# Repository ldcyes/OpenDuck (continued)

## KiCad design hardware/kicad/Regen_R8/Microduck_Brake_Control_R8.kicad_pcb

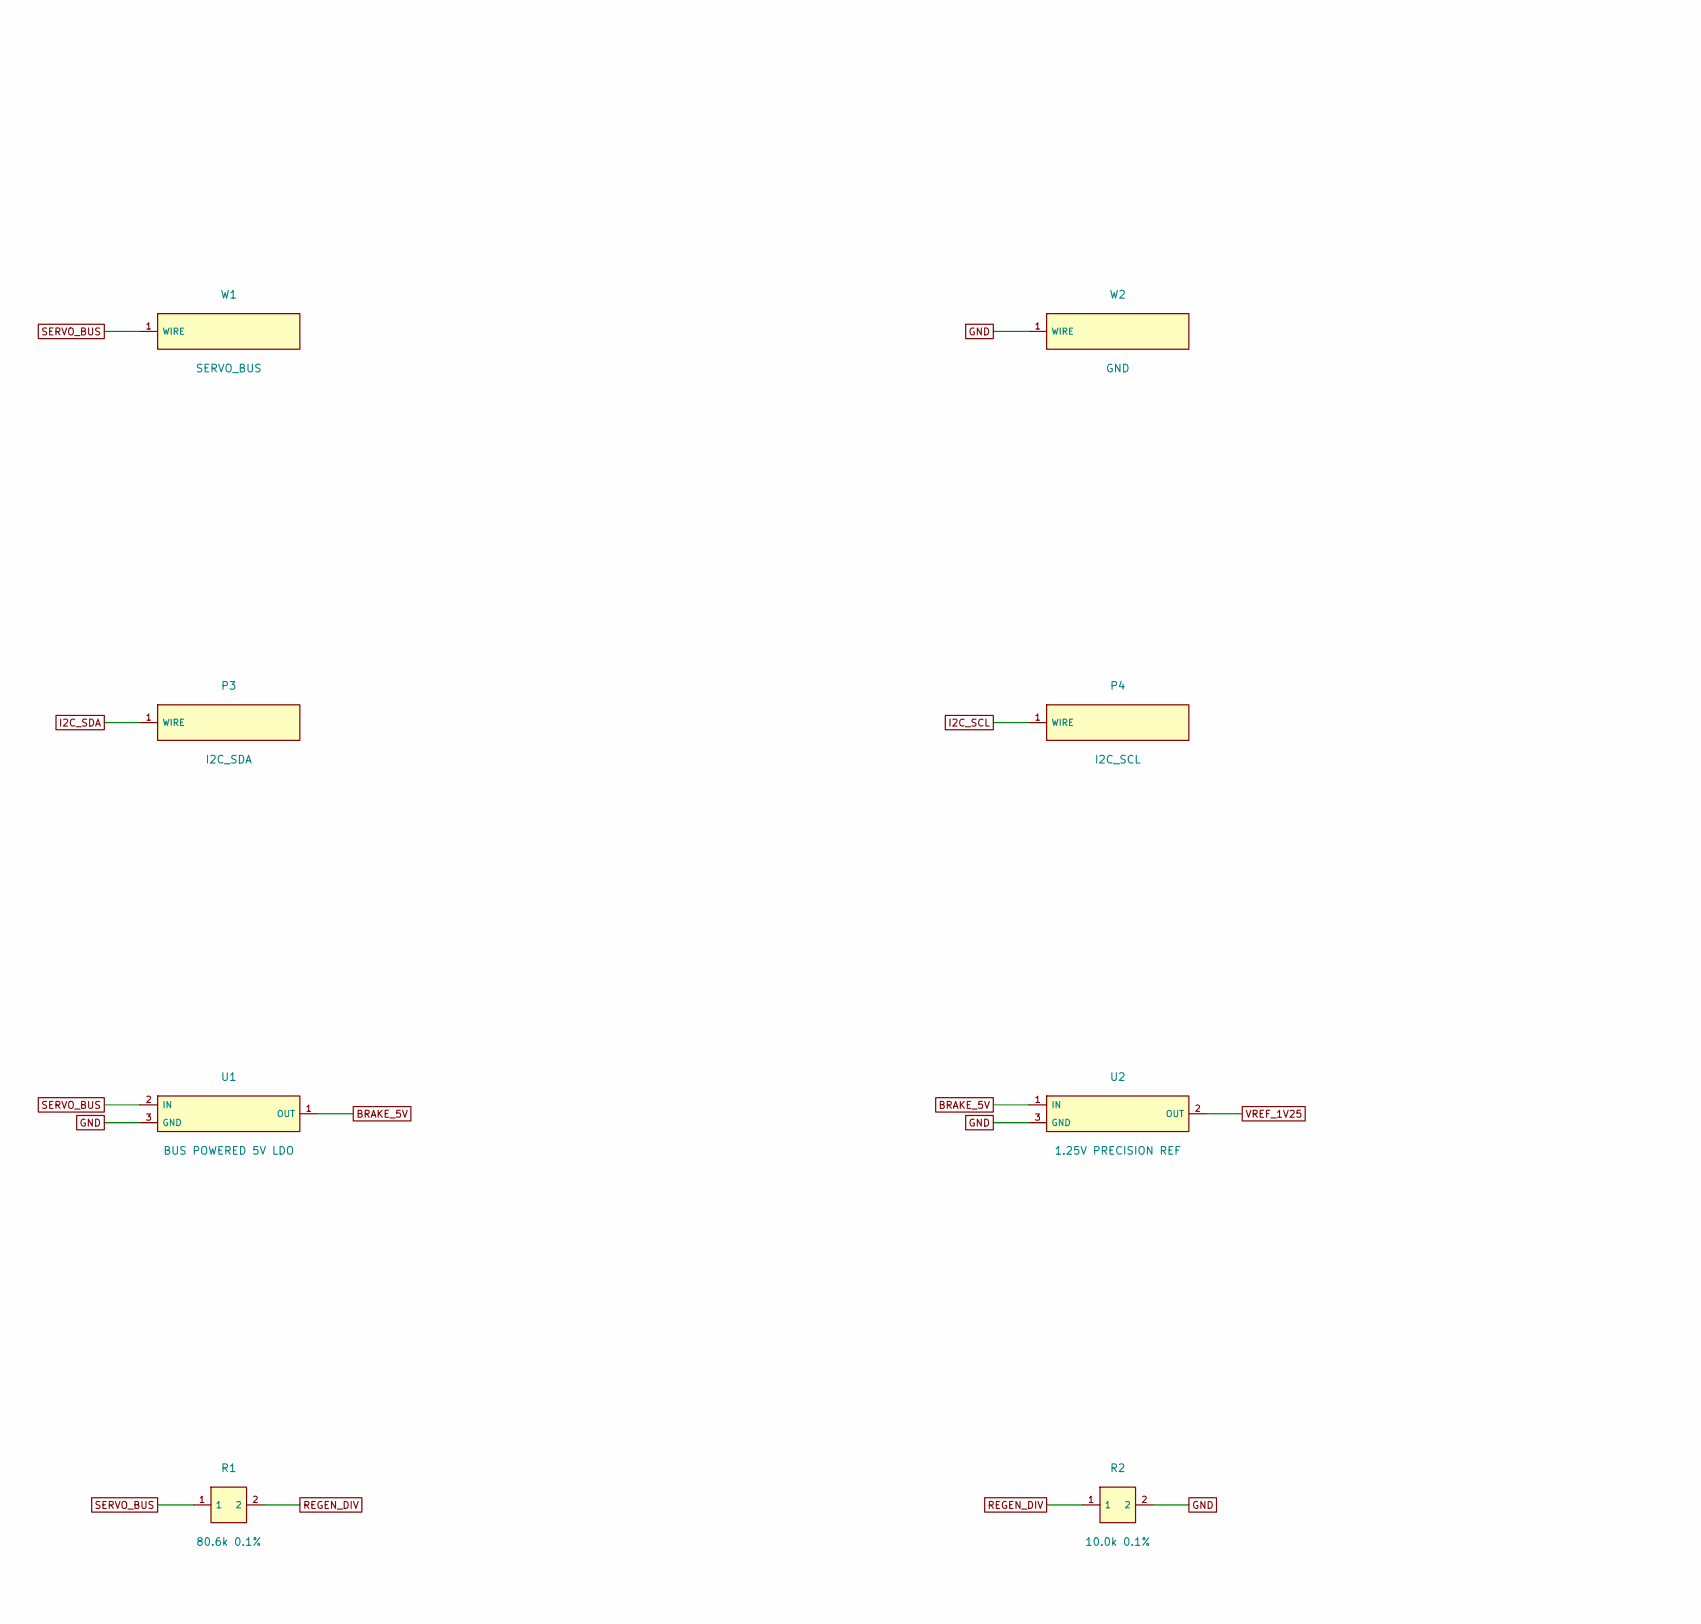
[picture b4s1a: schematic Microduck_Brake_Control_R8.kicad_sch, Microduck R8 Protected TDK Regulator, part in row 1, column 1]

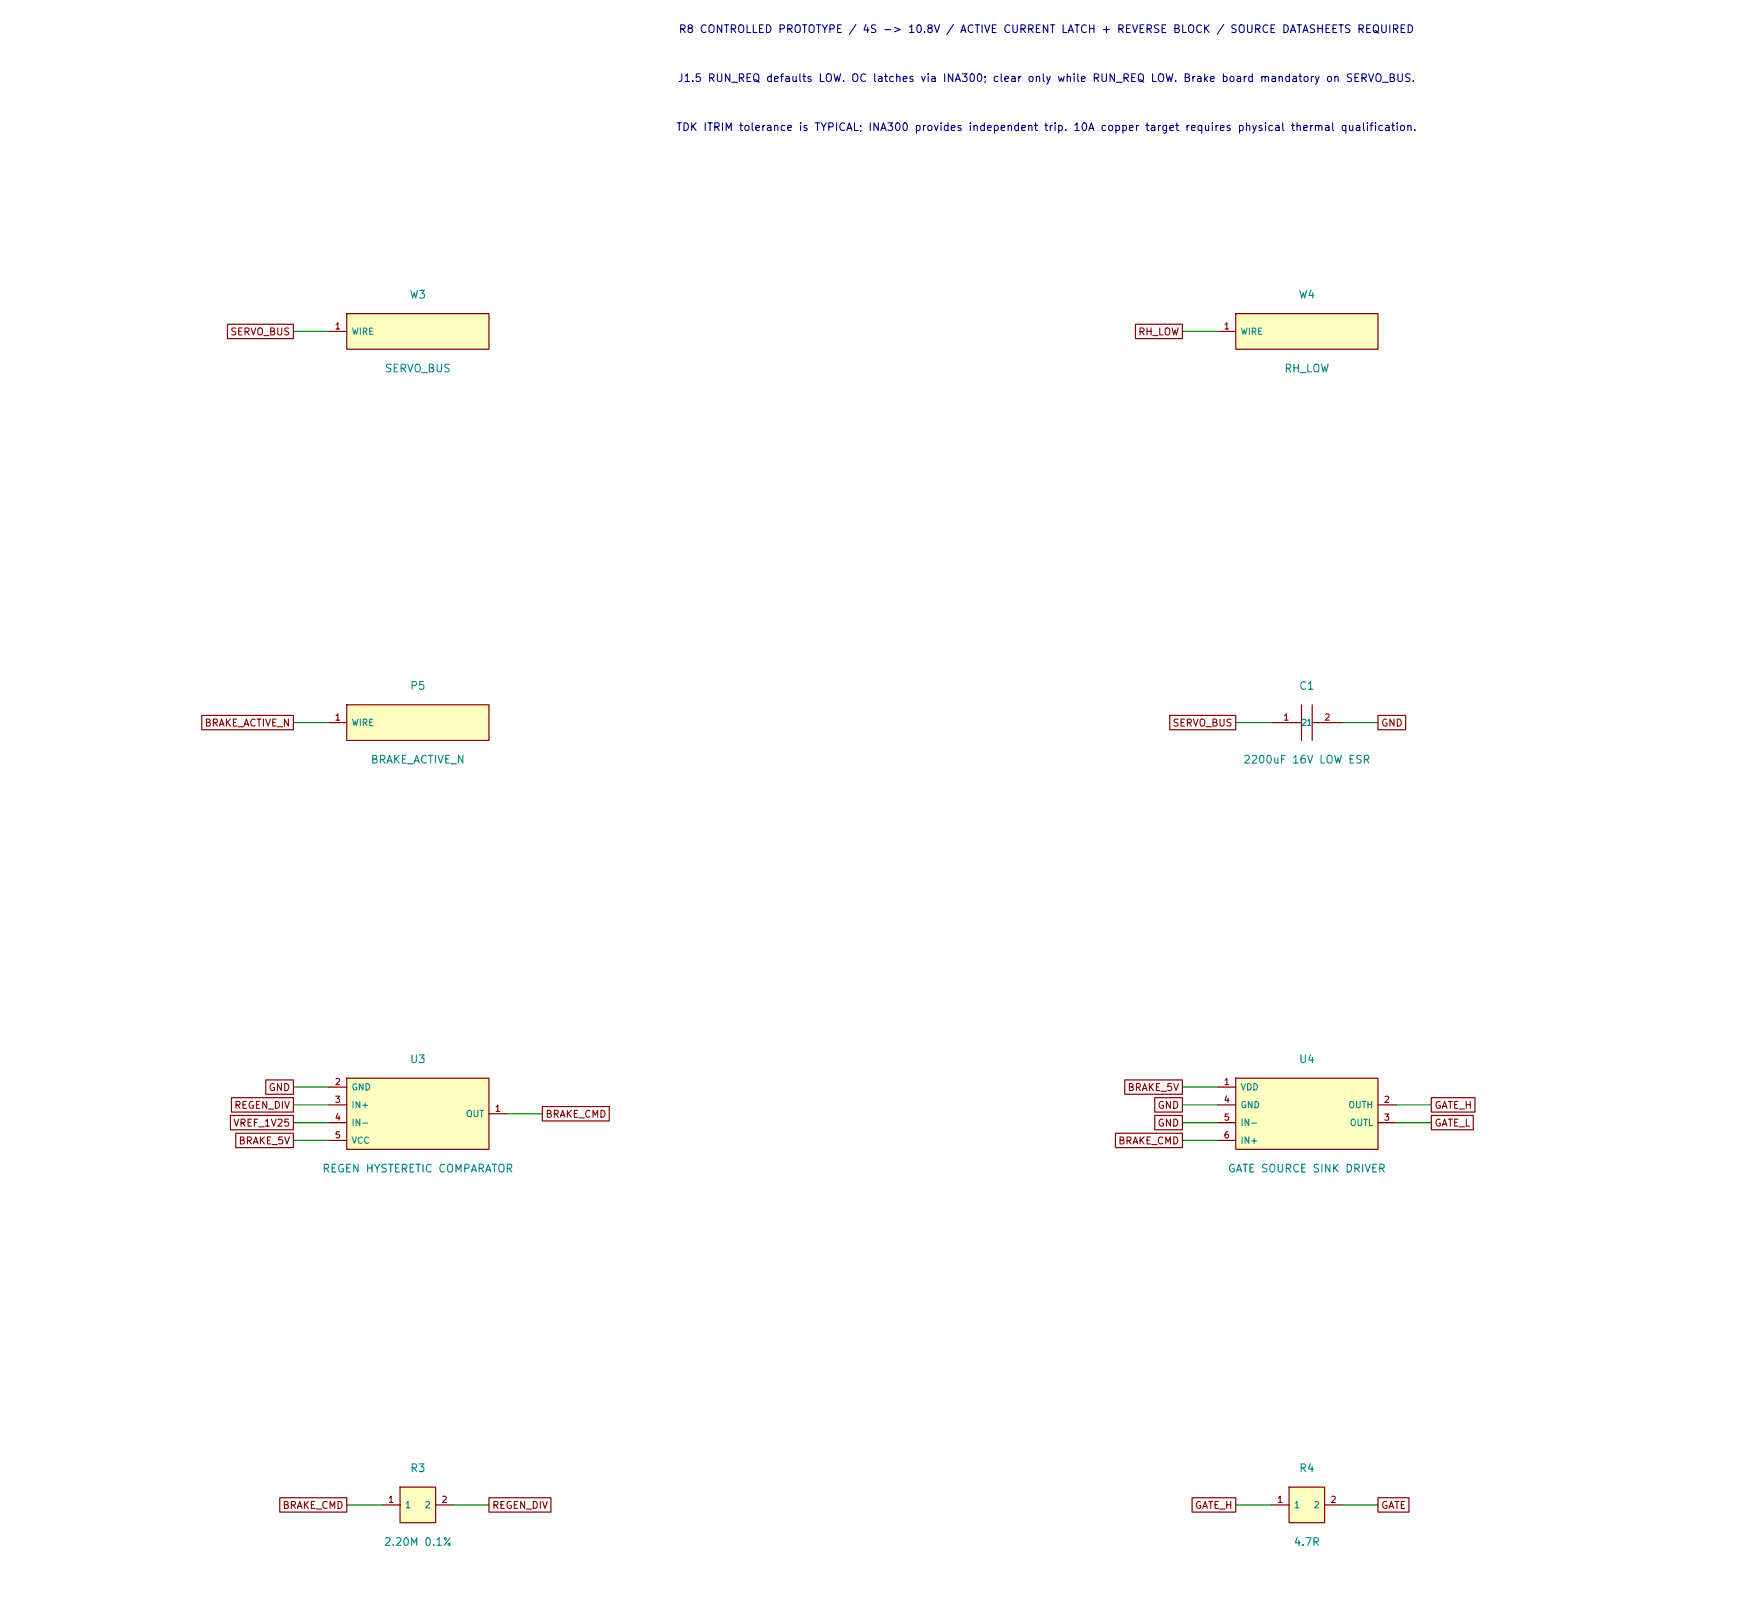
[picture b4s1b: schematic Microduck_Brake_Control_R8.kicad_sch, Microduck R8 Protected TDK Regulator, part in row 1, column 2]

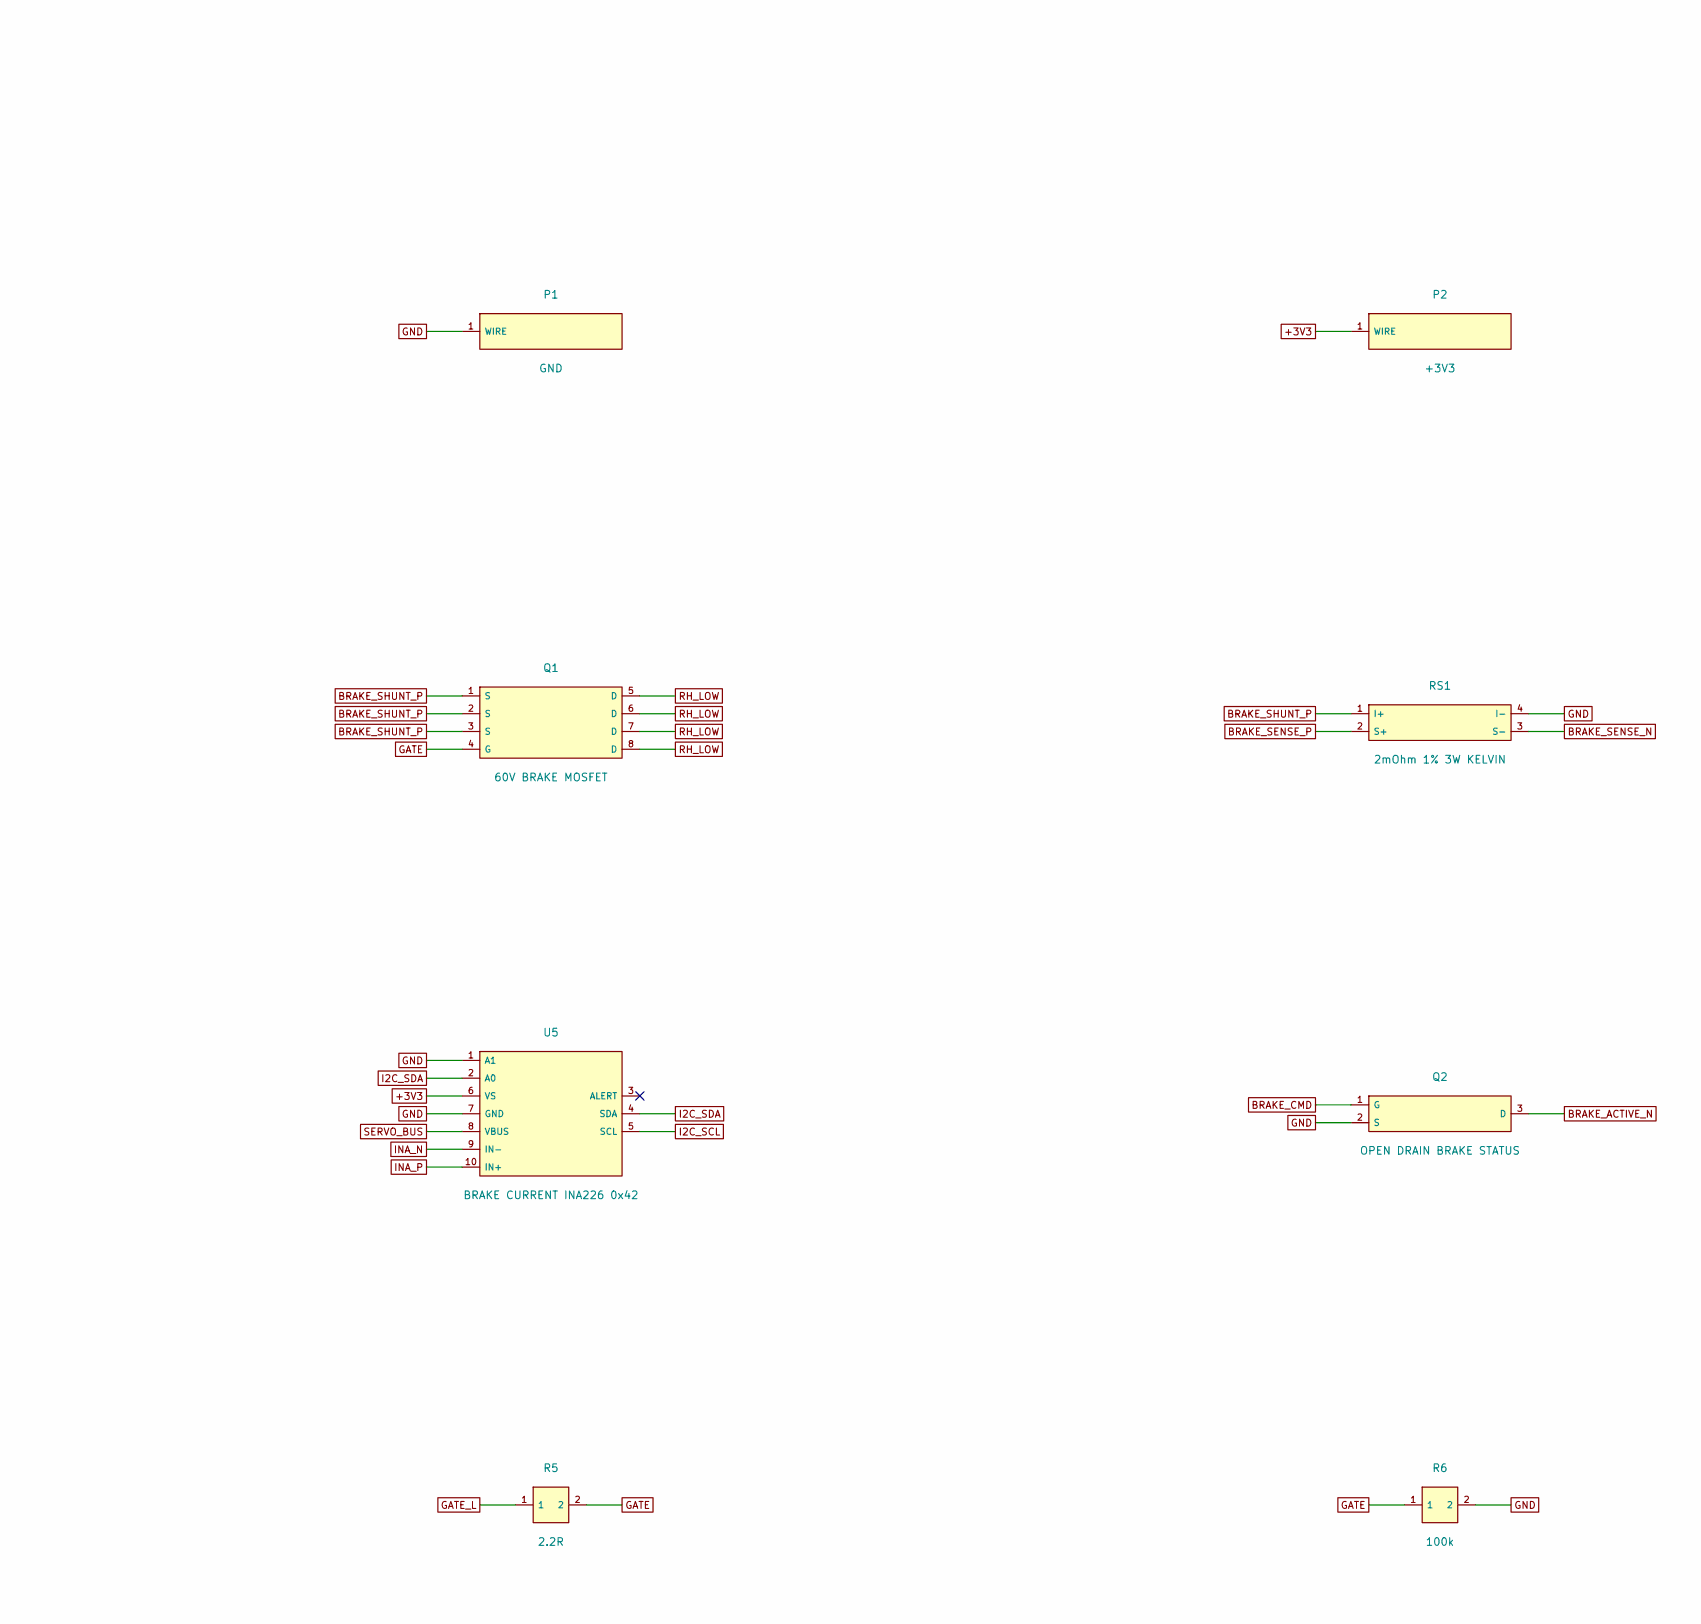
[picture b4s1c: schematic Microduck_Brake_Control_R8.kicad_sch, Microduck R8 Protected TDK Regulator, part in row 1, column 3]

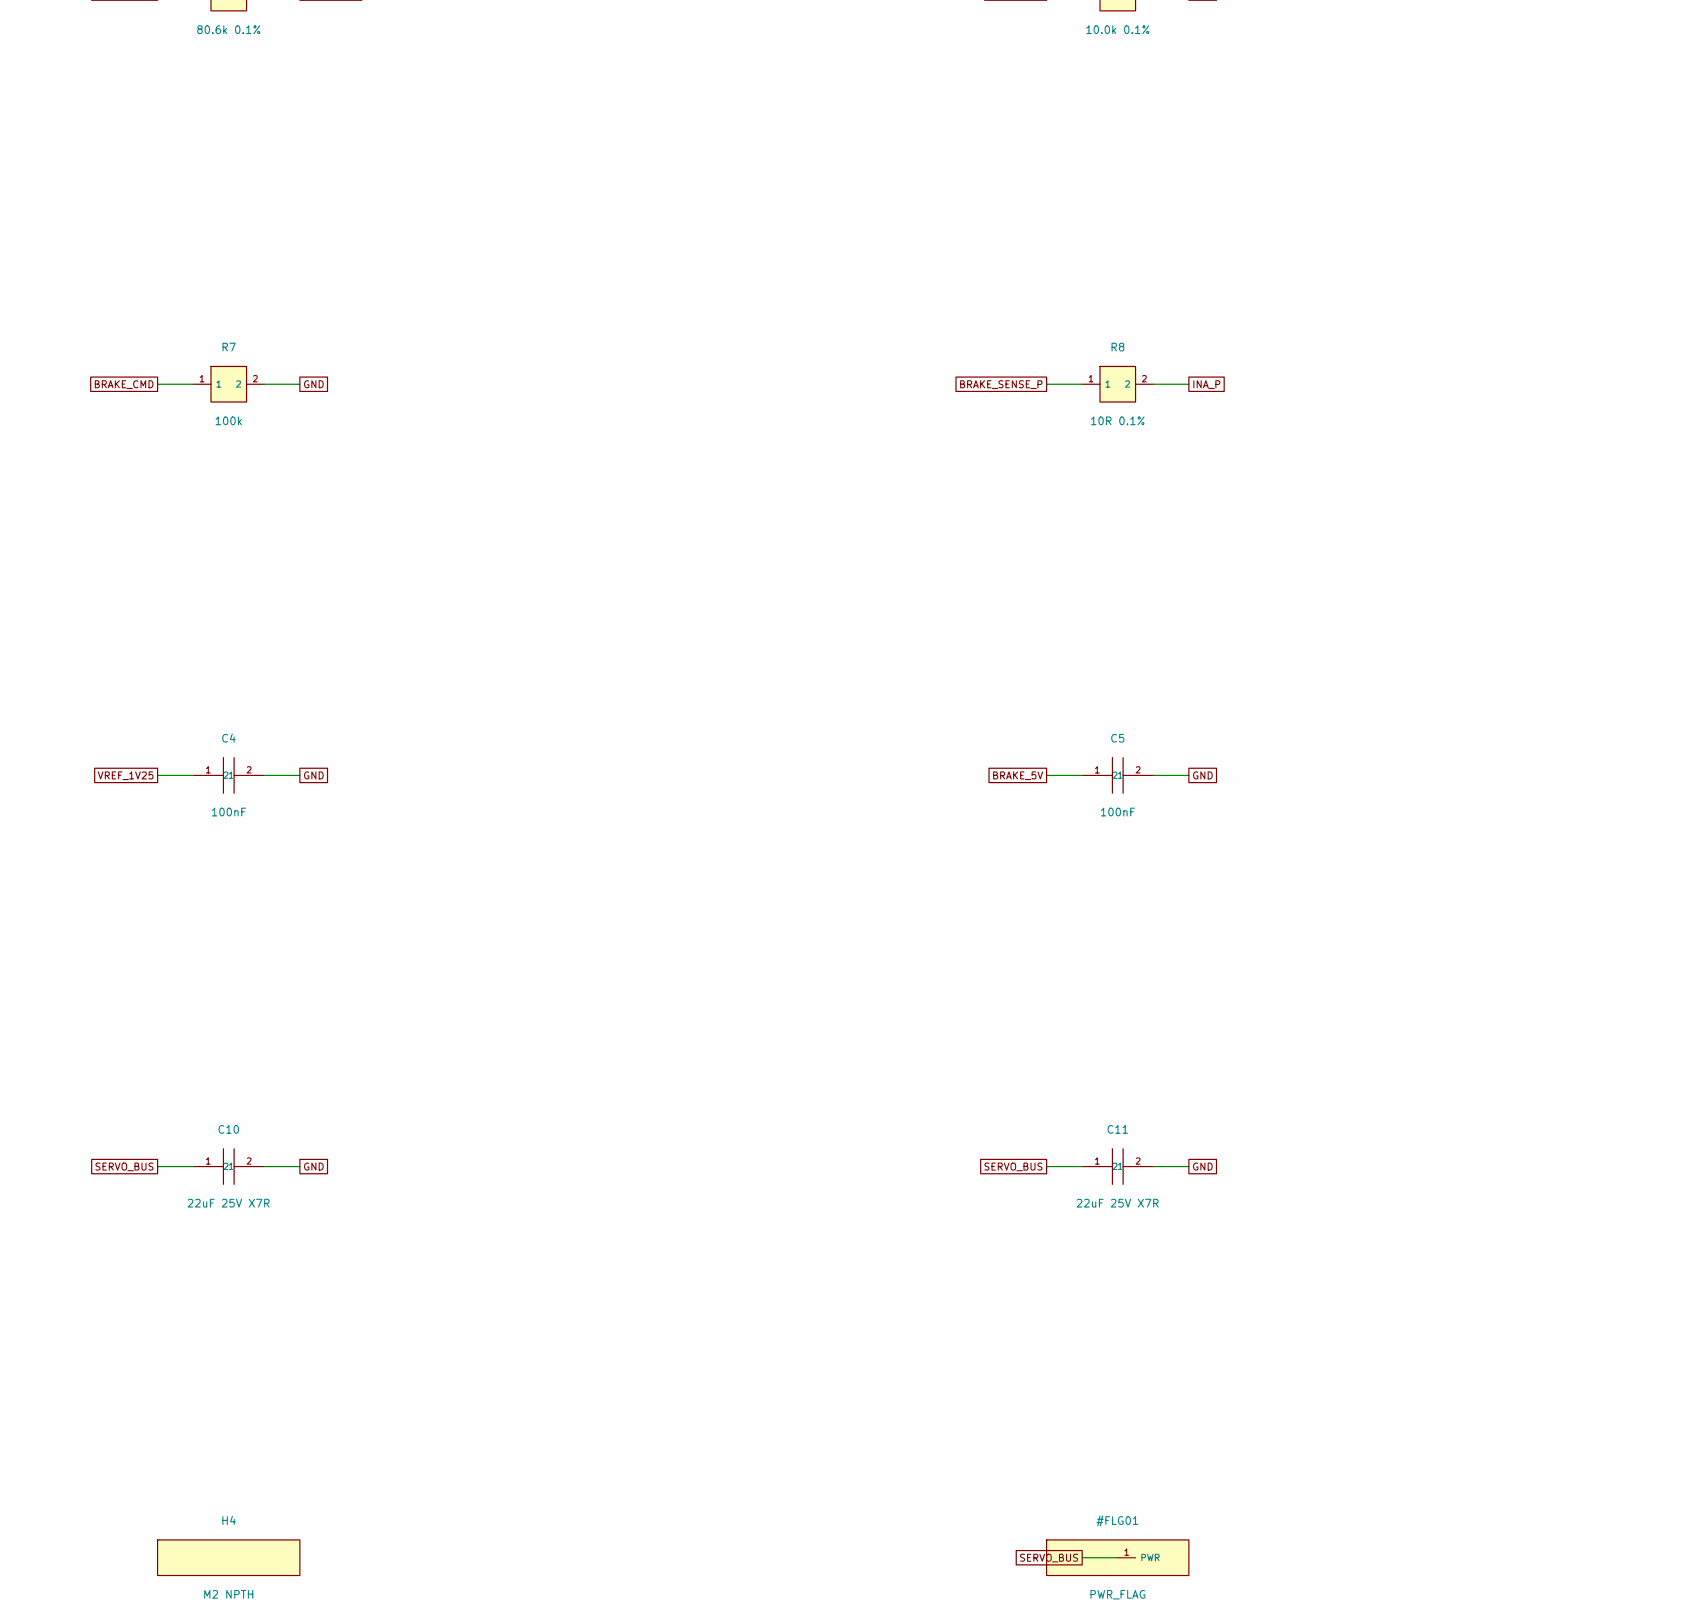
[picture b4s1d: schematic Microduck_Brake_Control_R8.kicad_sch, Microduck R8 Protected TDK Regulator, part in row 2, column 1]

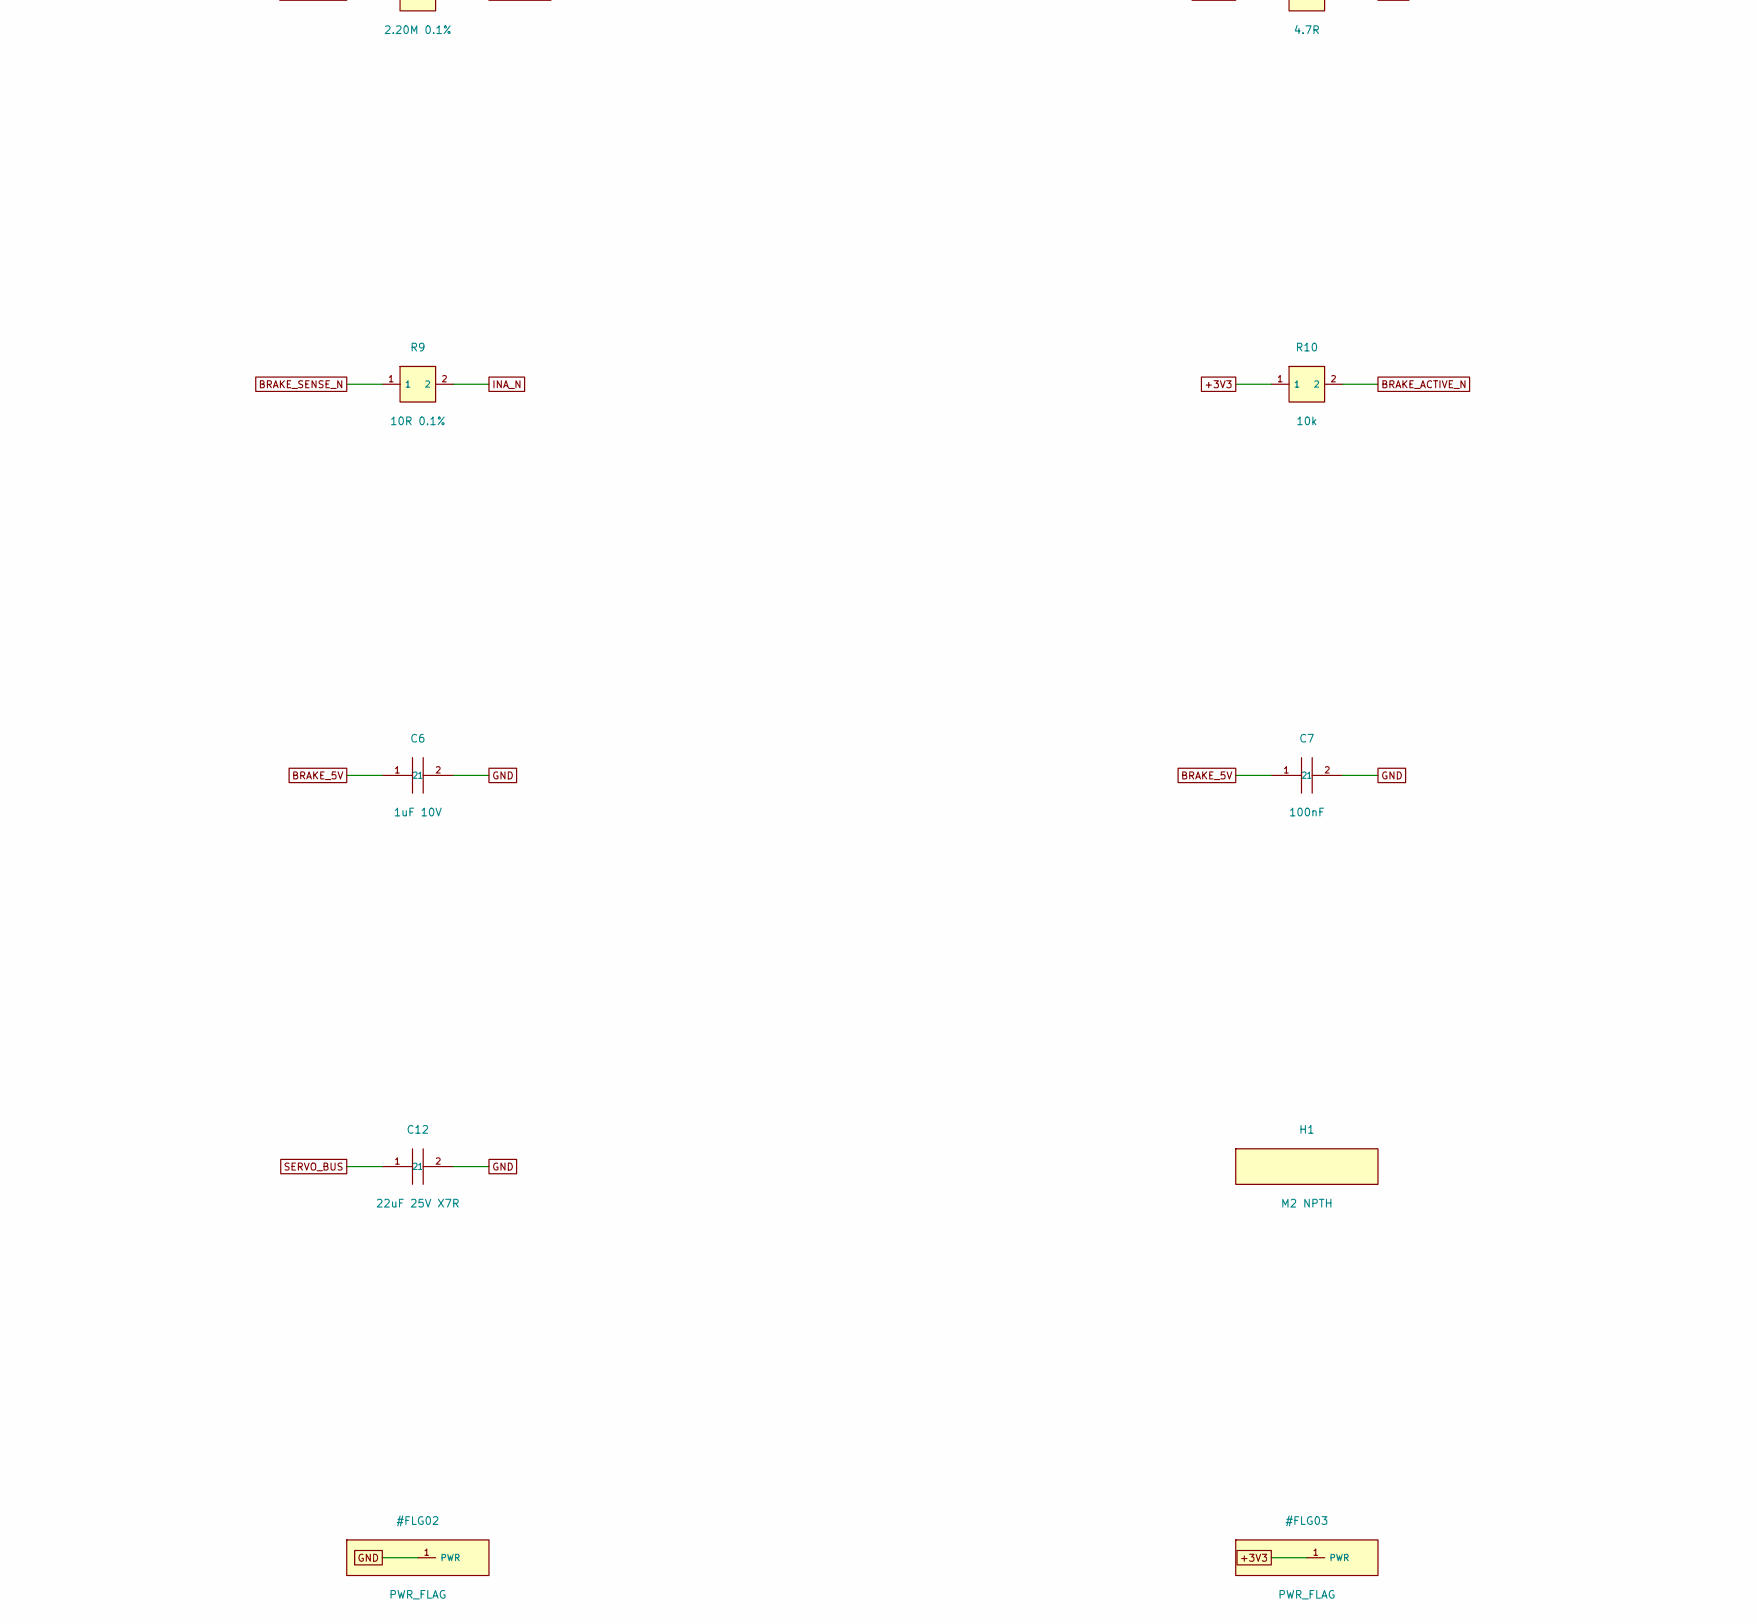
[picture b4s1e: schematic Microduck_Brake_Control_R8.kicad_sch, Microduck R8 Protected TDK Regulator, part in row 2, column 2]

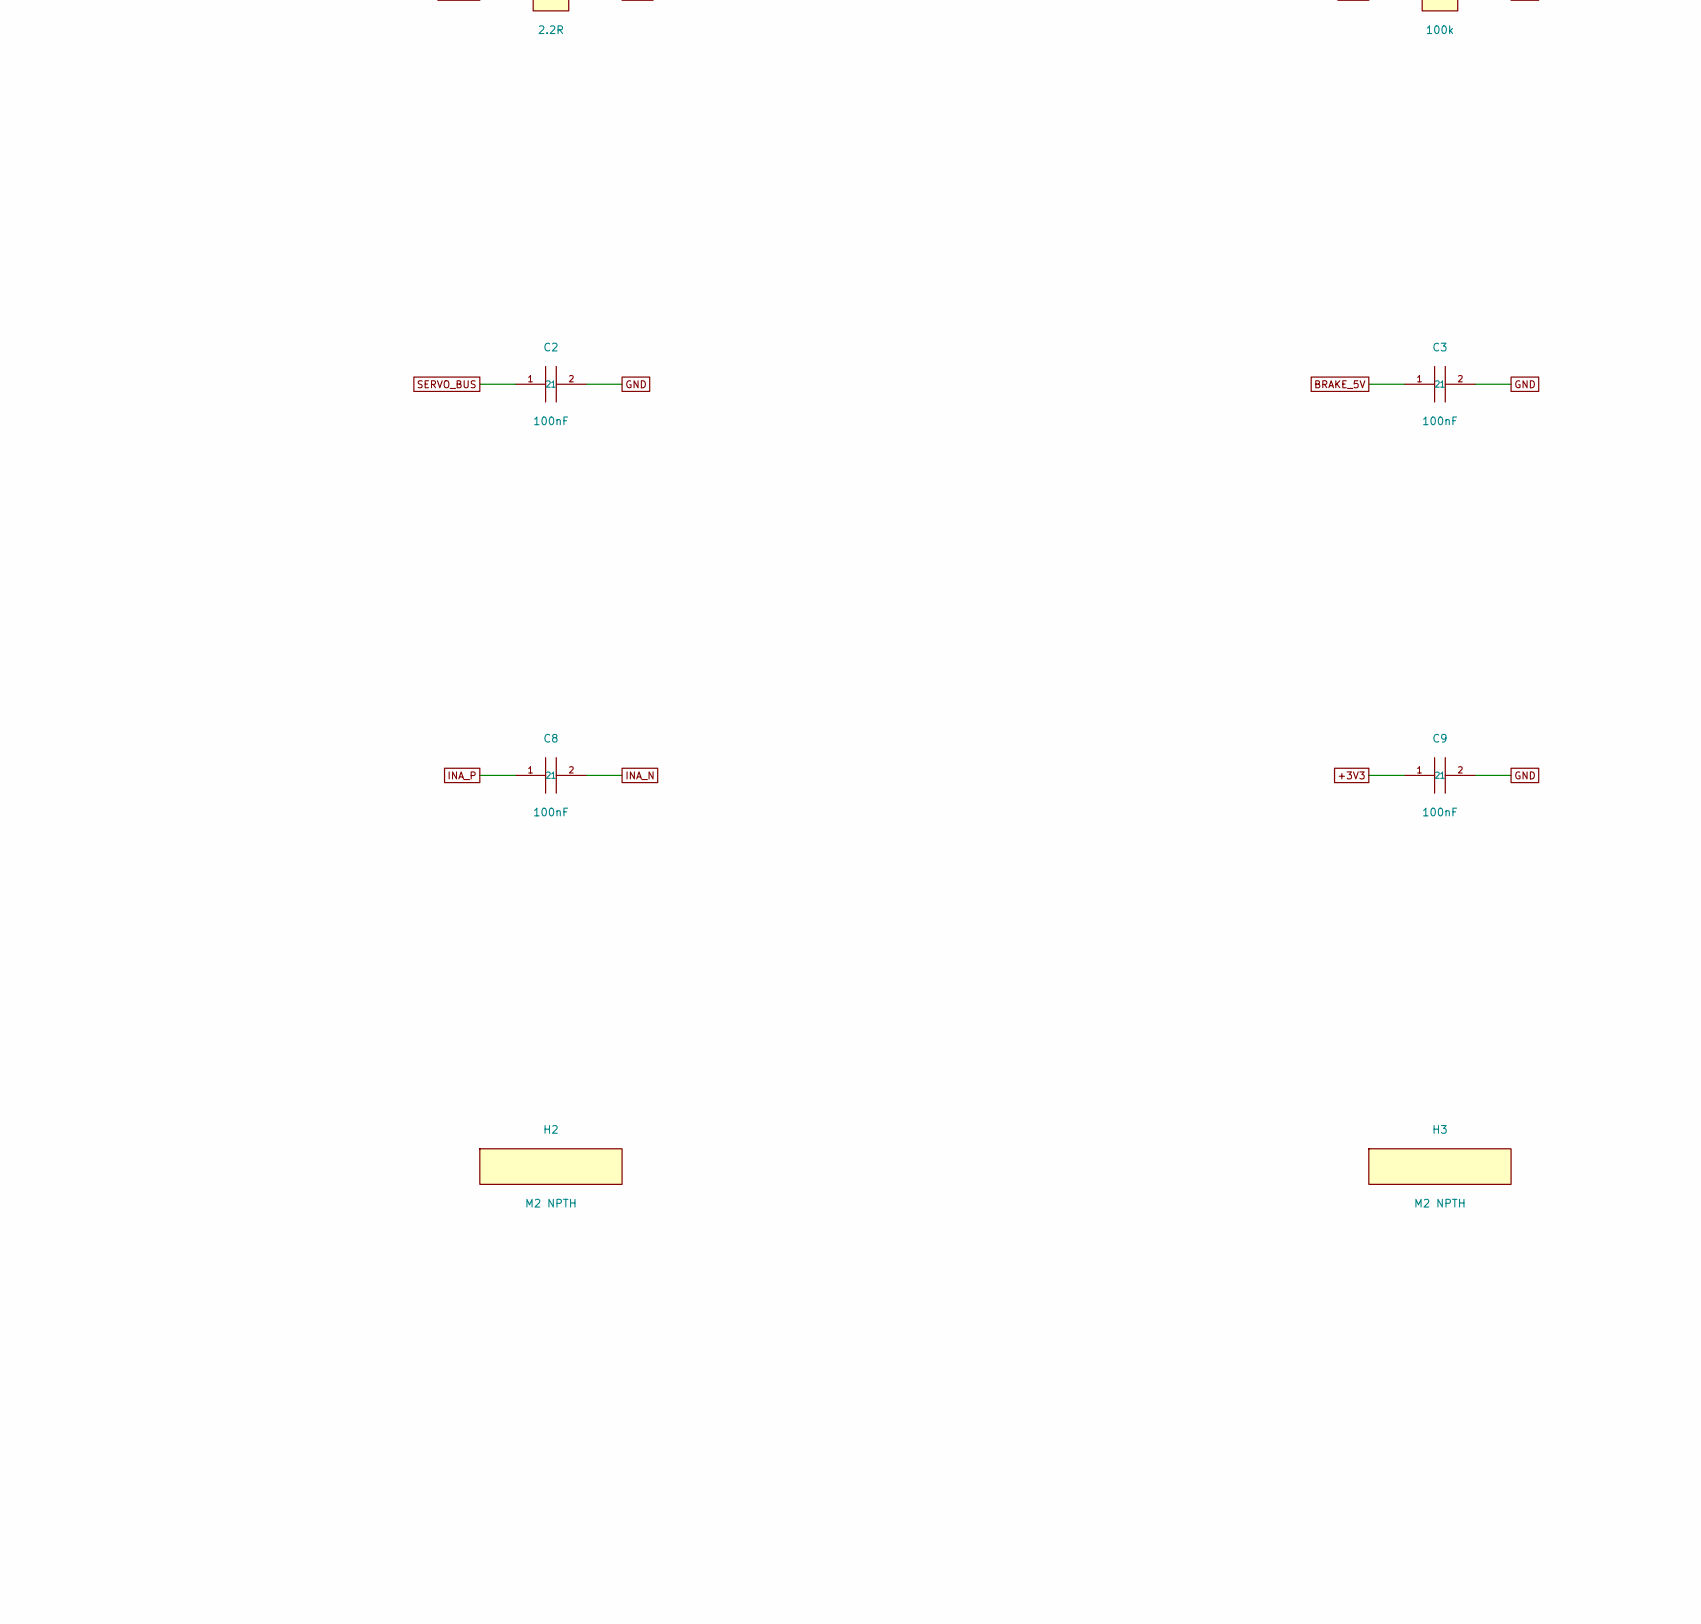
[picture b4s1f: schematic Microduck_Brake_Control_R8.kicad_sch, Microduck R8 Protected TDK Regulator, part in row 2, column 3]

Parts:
C1: 2200uF 16V LOW ESR; CP_Radial_D12.5mm_P5.00mm; MPN EEUFR1C222
C2, C3, C4, C5, C7, C8, C9: 100nF; C_0603_1608Metric; MPN GRM188R71H104KA93D
C6: 1uF 10V; C_0603_1608Metric; MPN GRM188R71A105KA61D
C10, C11, C12: 22uF 25V X7R; C_1210_3225Metric; MPN GRM32ER71E226KE15L
H1, H2, H3, H4: M2 NPTH; MountingHole_2.2mm_M2; MPN NO PART
P1: GND; WireSignal_0p5mm; MPN SOLDER AWG28 PIGTAIL
P2: +3V3; WireSignal_0p5mm; MPN SOLDER AWG28 PIGTAIL
P3: I2C_SDA; WireSignal_0p5mm; MPN SOLDER AWG28 PIGTAIL
P4: I2C_SCL; WireSignal_0p5mm; MPN SOLDER AWG28 PIGTAIL
P5: BRAKE_ACTIVE_N; WireSignal_0p5mm; MPN SOLDER AWG28 PIGTAIL
Q1: 60V BRAKE MOSFET; CSD18540Q5B_DNK; MPN CSD18540Q5B
Q2: OPEN DRAIN BRAKE STATUS; SOT-23; MPN BSS138
R1: 80.6k 0.1%; R_0603_1608Metric; MPN RT0603BRD0780K6L
R2: 10.0k 0.1%; R_0603_1608Metric; MPN RT0603BRD0710KL
R3: 2.20M 0.1%; R_0603_1608Metric; MPN RT0603BRD072M2L
R4: 4.7R; R_0603_1608Metric; MPN ERJ-3EKF4R7V
R5: 2.2R; R_0603_1608Metric; MPN ERJ-3EKF2R2V
R6, R7: 100k; R_0603_1608Metric; MPN ERJ-3EKF1003V
R8, R9: 10R 0.1%; R_0603_1608Metric; MPN RT0603BRD0710RL
R10: 10k; R_0603_1608Metric; MPN ERJ-3EKF1002V
RS1: 2mOhm 1% 3W KELVIN; WSL2726_Kelvin; MPN WSL27262L000FEA
U1: BUS POWERED 5V LDO; SOT-23; MPN TLV76050DBZR
U2: 1.25V PRECISION REF; SOT-23; MPN REF3312AIDBZR
U3: REGEN HYSTERETIC COMPARATOR; SOT-23-5; MPN TLV3201AIDBVR
U4: GATE SOURCE SINK DRIVER; SOT-23-6; MPN UCC27511DBVR
U5: BRAKE CURRENT INA226 0x42; MSOP-10_3x3mm_P0.5mm; MPN INA226AIDGSR
W1, W3: SERVO_BUS; WirePad_2p4mm_6mm; MPN SOLDER AWG16
W2: GND; WirePad_2p4mm_6mm; MPN SOLDER AWG16
W4: RH_LOW; WirePad_2p4mm_6mm; MPN SOLDER AWG16

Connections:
+3V3: C9.1, P2.1, R10.1, U5.6 (VS)
BRAKE_5V: C3.1, C5.1, C6.1, C7.1, U1.1 (OUT), U2.1 (IN), U3.5 (VCC), U4.1 (VDD)
BRAKE_ACTIVE_N: P5.1, Q2.3 (D), R10.2
BRAKE_CMD: Q2.1 (G), R3.1, R7.1, U3.1 (OUT), U4.6 (IN+)
BRAKE_SENSE_N: R9.1, RS1.3 (S-)
BRAKE_SENSE_P: R8.1, RS1.2 (S+)
BRAKE_SHUNT_P: Q1.1 (S), Q1.2 (S), Q1.3 (S), RS1.1 (I+)
GATE: Q1.4 (G), R4.2, R5.2, R6.1
GATE_H: R4.1, U4.2 (OUTH)
GATE_L: R5.1, U4.3 (OUTL)
GND: C1.2, C2.2, C3.2, C4.2, C5.2, C6.2, C7.2, C9.2, C10.2, C11.2, C12.2, P1.1, Q2.2 (S), R2.2, R6.2, R7.2, RS1.4 (I-), U1.3 (GND), U2.3 (GND), U3.2 (GND), U4.4 (GND), U4.5 (IN-), U5.1 (A1), U5.7 (GND), W2.1
I2C_SCL: P4.1, U5.5 (SCL)
I2C_SDA: P3.1, U5.2 (A0), U5.4 (SDA)
INA_N: C8.2, R9.2, U5.9 (IN-)
INA_P: C8.1, R8.2, U5.10 (IN+)
REGEN_DIV: R1.2, R2.1, R3.2, U3.3 (IN+)
RH_LOW: Q1.5 (D), Q1.6 (D), Q1.7 (D), Q1.8 (D), W4.1
SERVO_BUS: C1.1, C2.1, C10.1, C11.1, C12.1, R1.1, U1.2 (IN), U5.8 (VBUS), W1.1, W3.1
VREF_1V25: C4.1, U2.2 (OUT), U3.4 (IN-)

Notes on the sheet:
R8 CONTROLLED PROTOTYPE / 4S -> 10.8V / ACTIVE CURRENT LATCH + REVERSE BLOCK / SOURCE DATASHEETS REQUIRED
J1.5 RUN_REQ defaults LOW. OC latches via INA300; clear only while RUN_REQ LOW. Brake board mandatory on SERVO_BUS.
TDK ITRIM tolerance is TYPICAL; INA300 provides independent trip. 10A copper target requires physical thermal qualification.

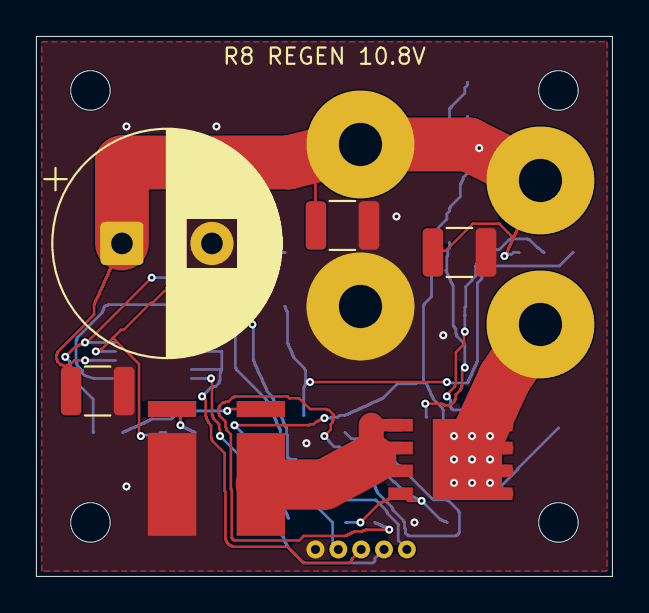
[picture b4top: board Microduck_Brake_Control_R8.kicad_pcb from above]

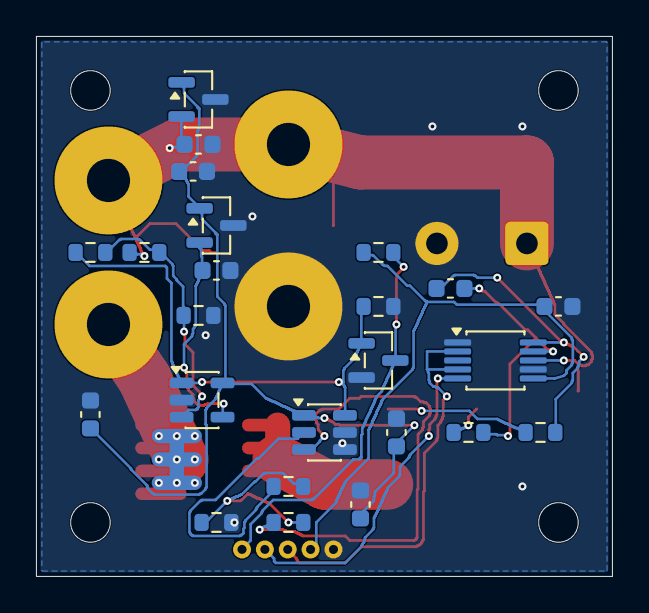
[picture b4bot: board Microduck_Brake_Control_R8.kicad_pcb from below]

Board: 2 copper layers, 32.0 x 30.0 mm, 43 parts (24 on the bottom side), 19 nets.

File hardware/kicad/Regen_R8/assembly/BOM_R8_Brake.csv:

reference,value,MPN,footprint,side,x_mm,y_mm,rotation_deg,datasheet
W1,SERVO_BUS,SOLDER AWG16,Microduck_Brake_R8:WirePad_2p4mm_6mm,F,18,6,0,
W2,GND,SOLDER AWG16,Microduck_Brake_R8:WirePad_2p4mm_6mm,F,18,15,0,
W3,SERVO_BUS,SOLDER AWG16,Microduck_Brake_R8:WirePad_2p4mm_6mm,F,28,8,0,
W4,RH_LOW,SOLDER AWG16,Microduck_Brake_R8:WirePad_2p4mm_6mm,F,28,16,0,
P1,GND,SOLDER AWG28 PIGTAIL,Microduck_Brake_R8:WireSignal_0p5mm,F,15.5,28.5,0,
P2,+3V3,SOLDER AWG28 PIGTAIL,Microduck_Brake_R8:WireSignal_0p5mm,F,16.77,28.5,0,
P3,I2C_SDA,SOLDER AWG28 PIGTAIL,Microduck_Brake_R8:WireSignal_0p5mm,F,18.04,28.5,0,
P4,I2C_SCL,SOLDER AWG28 PIGTAIL,Microduck_Brake_R8:WireSignal_0p5mm,F,19.31,28.5,0,
P5,BRAKE_ACTIVE_N,SOLDER AWG28 PIGTAIL,Microduck_Brake_R8:WireSignal_0p5mm,F,20.58,28.5,0,
C1,2200uF 16V LOW ESR,EEUFR1C222,Capacitor_THT:CP_Radial_D12.5mm_P5.00mm,F,4.75,11.5,0,https://industrial.panasonic.com/cdbs/www-data/pdf/RDF0000/A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
Q1,60V BRAKE MOSFET,CSD18540Q5B,Microduck_Brake_R8:CSD18540Q5B_DNK,F,23,23.5,180,https://www.ti.com/lit/ds/symlink/csd18540q5b.pdf
RS1,2mOhm 1% 3W KELVIN,WSL27262L000FEA,Microduck_Brake_R8:WSL2726_Kelvin,F,10,24,180,https://www.vishay.com/docs/30131/wsl2726.pdf
U1,BUS POWERED 5V LDO,TLV76050DBZR,Package_TO_SOT_SMD:SOT-23,B,23,3.5,0,https://www.ti.com/lit/ds/symlink/tlv760.pdf
U2,1.25V PRECISION REF,REF3312AIDBZR,Package_TO_SOT_SMD:SOT-23,B,22,10.5,0,https://www.ti.com/lit/ds/symlink/ref33.pdf
U3,REGEN HYSTERETIC COMPARATOR,TLV3201AIDBVR,Package_TO_SOT_SMD:SOT-23-5,B,22.8,20.2,0,https://www.ti.com/lit/ds/symlink/tlv3201.pdf
U4,GATE SOURCE SINK DRIVER,UCC27511DBVR,Package_TO_SOT_SMD:SOT-23-6,B,16,22,0,https://www.ti.com/lit/ds/symlink/ucc27511.pdf
U5,BRAKE CURRENT INA226 0x42,INA226AIDGSR,Package_SO:MSOP-10_3x3mm_P0.5mm,B,6.5,18,0,https://www.ti.com/lit/ds/symlink/ina226.pdf
Q2,OPEN DRAIN BRAKE STATUS,BSS138,Package_TO_SOT_SMD:SOT-23,B,13,18,0,https://www.onsemi.com/pdf/datasheet/bss138-d.pdf
R1,80.6k 0.1%,RT0603BRD0780K6L,Resistor_SMD:R_0603_1608Metric,B,26,12,0,
R2,10.0k 0.1%,RT0603BRD0710KL,Resistor_SMD:R_0603_1608Metric,B,23,15.5,0,
R3,2.20M 0.1%,RT0603BRD072M2L,Resistor_SMD:R_0603_1608Metric,B,29,12,0,
R4,4.7R,ERJ-3EKF4R7V,Resistor_SMD:R_0603_1608Metric,B,18,25,0,
R5,2.2R,ERJ-3EKF2R2V,Resistor_SMD:R_0603_1608Metric,B,18,27,0,
R6,100k,ERJ-3EKF1003V,Resistor_SMD:R_0603_1608Metric,B,22,27,0,
R7,100k,ERJ-3EKF1003V,Resistor_SMD:R_0603_1608Metric,B,13,15,0,
R8,10R 0.1%,RT0603BRD0710RL,Resistor_SMD:R_0603_1608Metric,B,4,22,0,
R9,10R 0.1%,RT0603BRD0710RL,Resistor_SMD:R_0603_1608Metric,B,8,22,0,
R10,10k,ERJ-3EKF1002V,Resistor_SMD:R_0603_1608Metric,B,13,12,0,
C2,100nF,GRM188R71H104KA93D,Capacitor_SMD:C_0603_1608Metric,B,23,6,0,
C3,100nF,GRM188R71H104KA93D,Capacitor_SMD:C_0603_1608Metric,B,23.3,7.5,0,
C4,100nF,GRM188R71H104KA93D,Capacitor_SMD:C_0603_1608Metric,B,22,13,0,
C5,100nF,GRM188R71H104KA93D,Capacitor_SMD:C_0603_1608Metric,B,29,21,90,
C6,1uF 10V,GRM188R71A105KA61D,Capacitor_SMD:C_0603_1608Metric,B,12,22,90,
C7,100nF,GRM188R71H104KA93D,Capacitor_SMD:C_0603_1608Metric,B,14,26,90,
C8,100nF,GRM188R71H104KA93D,Capacitor_SMD:C_0603_1608Metric,B,9,14,0,
C9,100nF,GRM188R71H104KA93D,Capacitor_SMD:C_0603_1608Metric,B,3,15,0,
C10,22uF 25V X7R,GRM32ER71E226KE15L,Capacitor_SMD:C_1210_3225Metric,F,3.4,19.7,0,https://search.murata.co.jp/Ceramy/image/img/A01X/G101/ENG/G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
C11,22uF 25V X7R,GRM32ER71E226KE15L,Capacitor_SMD:C_1210_3225Metric,F,17,10.5,0,https://search.murata.co.jp/Ceramy/image/img/A01X/G101/ENG/G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
C12,22uF 25V X7R,GRM32ER71E226KE15L,Capacitor_SMD:C_1210_3225Metric,F,23.5,12,0,https://search.murata.co.jp/Ceramy/image/img/A01X/G101/ENG/G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
H1,M2 NPTH,NO PART,MountingHole:MountingHole_2.2mm_M2,F,3,3,0,
H2,M2 NPTH,NO PART,MountingHole:MountingHole_2.2mm_M2,F,29,3,0,
H3,M2 NPTH,NO PART,MountingHole:MountingHole_2.2mm_M2,F,3,27,0,
H4,M2 NPTH,NO PART,MountingHole:MountingHole_2.2mm_M2,F,29,27,0,
